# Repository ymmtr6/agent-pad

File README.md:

# AgentPad

RP2040-Zero を使った、8 キー＋ロータリーエンコーダーのマクロパッドです。基板（KiCad）、3D プリント外装・キーキャップ、QMK ファームウェア、VIA 定義をまとめています。

現行版は **Rev2**（単一基板・裏面ホットスワップ）です。

## Rev2 の仕様

- 基板：62 × 80 × 1.6 mm、四隅に M2 用 Ø2.2 mm 穴
- キー：MX 互換スイッチ 8 個（19.05 mm ピッチ、3+3+2 配列）
- ソケット：Kailh CPG151101S11（基板裏面に実装、スイッチは表面から挿す）
- エンコーダー：EC11（右下、押し込み付き）
- MCU：Waveshare RP2040-Zero-M
- USB VID/PID：`0x4150` / `0xA902`

詳しい寸法は [docs/REV2_SINGLE_PCB.md](docs/REV2_SINGLE_PCB.md) と [manifest_rev2.json](manifest_rev2.json) を参照してください。

## デフォルトのキーマップ

| | 左 | 中央 | 右 |
| --- | --- | --- | --- |
| 上段 | F13 | F14 | F15 |
| 中段 | F16 | F17 | F18 |
| 下段 | F19 | F20 | エンコーダー押し込み：Mute |

エンコーダーは反時計回りで音量を下げ、時計回りで上げます。

macOS では F14/F15 が標準で画面の明るさに割り当てられています。システム設定 > キーボード > キーボードショートカット > ディスプレイ で無効にするか、キーを割り当て直してください。

## ファームウェアの書き込み

ビルド済みの UF2 が [firmware/build/](firmware/build/) にあります。

| ファイル | 内容 |
| --- | --- |
| `agent_pad_rev2_via.uf2` | VIA 対応版（キーマップを VIA で変更できる） |
| `agent_pad_rev2_default.uf2` | 固定キーマップ版 |

1. データ通信対応の USB-C ケーブルで PC につなぐ。
2. BOOT と RESET を同時に押し、RESET を離してから BOOT を離す。
3. `RPI-RP2` ドライブが現れたら、UF2 ファイルをコピーする。
4. ドライブが消え、`AgentPad Rev2` として再起動する。

RESET を素早く 2 回押してもブートローダーに入れます。

## VIA でキーマップを変更する

AgentPad は VIA の公式リストに登録していないため、定義ファイルを手動で読み込みます。先に VIA 対応版の UF2 を書き込んでおいてください。

1. [firmware/via/agentpad_rev2.json](firmware/via/agentpad_rev2.json) をダウンロードする。
2. Chrome または Edge で https://usevia.app を開く。
3. Settings で「Show Design tab」を有効にする。
4. Design タブの「Load Draft Definition」で、ダウンロードした JSON を選ぶ。
5. Configure タブで「Authorize device」を押し、`AgentPad Rev2` を選ぶ。

8 キーとエンコーダーの押し込み・左右回転を変更できます。

## ファームウェアのビルド

QMK Firmware の公式リポジトリにキーボード定義をコピーしてビルドします。

```sh
rsync -a firmware/qmk/keyboards/agent_pad/rev2/ \
  /path/to/qmk_firmware/keyboards/agent_pad/rev2/
cd /path/to/qmk_firmware
make agent_pad/rev2:via
```

詳しい手順と検証結果は [firmware/readme.md](firmware/readme.md) にあります。

## 基板の製造

JLCPCB に発注する Gerber は [manufacturing/agentpad_rev2_single_gerber.zip](manufacturing/agentpad_rev2_single_gerber.zip) です。発注設定は [docs/JLCPCB_ORDER_REV2.md](docs/JLCPCB_ORDER_REV2.md)、検証結果は [docs/VALIDATION_REV2.md](docs/VALIDATION_REV2.md) を参照してください。

基板データは生成スクリプトから作り直せます。

```sh
python3 -m venv .venv
.venv/bin/pip install -r requirements.txt
AGENTPAD_OUT=/tmp/agentpad_rev2_single_build .venv/bin/python scripts/generate_agentpad_rev2.py
scripts/run_kicad_drc.sh rev2
```

DRC の実行には KiCad 9 の `kicad-cli` が必要です。

## 外装とキーキャップ

- [cad/rev2_case/](cad/rev2_case/)：3D プリント外装（底トレイ、プレート）の OpenSCAD ソース、STL、G-code
- [cad/keycap_cherry_mx/](cad/keycap_cherry_mx/)：Cherry MX 互換キーキャップ

G-code は Creality Ender-3 V3 SE と PLA 用です。USB 接続での印刷手順は [docs/ENDER3_V3_SE_USB_PRINTING.md](docs/ENDER3_V3_SE_USB_PRINTING.md) を参照してください。

## ディレクトリ構成

| パス | 内容 |
| --- | --- |
| `kicad/` | KiCad 基板データとフットプリント |
| `scripts/` | 基板データの生成スクリプト、DRC 実行スクリプト |
| `gerber/`, `manufacturing/` | 生成済みの Gerber と発注用 ZIP |
| `firmware/` | QMK キーボード定義、ビルド済み UF2、VIA 定義 |
| `cad/` | 外装・キーキャップの 3D データ |
| `docs/` | 設計メモ、発注手順、検証結果、画像 |

Rev1（2 枚構成の旧版）のデータも含まれています。

## ライセンス

[MIT License](LICENSE) です。

ただし `firmware/` 以下は QMK Firmware 向けのコードと、QMK を含めてビルドした UF2 なので、QMK に合わせて GPL-2.0-or-later とします。

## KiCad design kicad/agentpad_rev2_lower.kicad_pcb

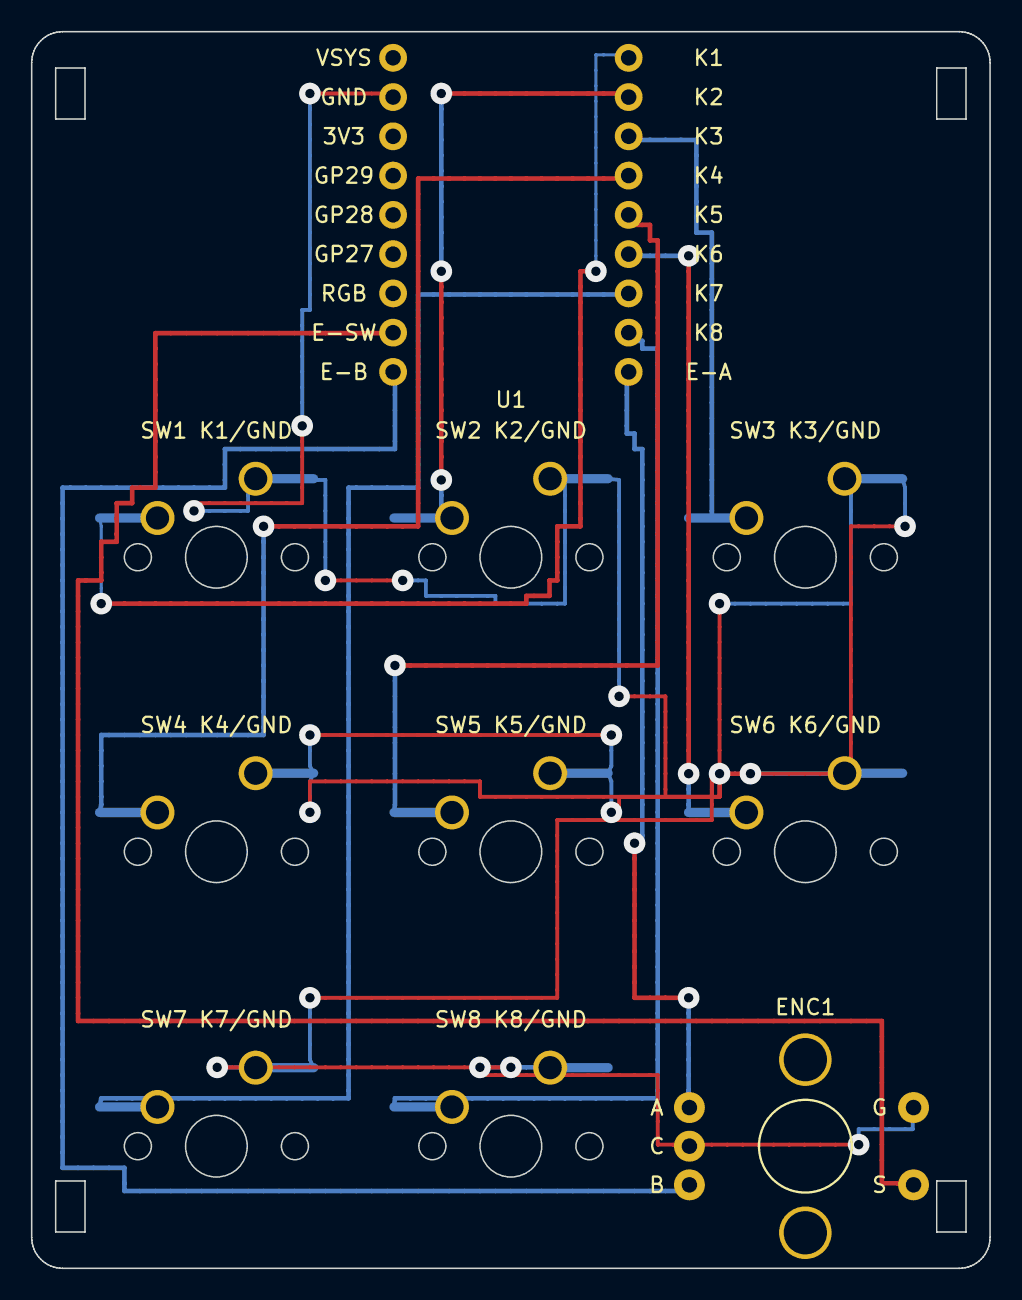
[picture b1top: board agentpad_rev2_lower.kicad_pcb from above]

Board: 2 copper layers, 62.0 x 80.0 mm, 10 parts (0 on the bottom side), 12 nets.

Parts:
ENC1: EC11E push encoder; RotaryEncoder_Alps_EC11E-Switch_Vertical_H20mm
SW1, SW2, SW3, SW4, SW5, SW6, SW7, SW8: Kailh MX Hotswap; Kailh_MX_Hotswap_1U
U1: RP2040-Zero-M (visible top); RP2040-Zero-M_Header_Top

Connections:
ENC_A: ENC1.A, U1.9
ENC_B: ENC1.B, U1.15
ENC_SW: ENC1.S1, U1.16
GND: ENC1.C, ENC1.S2, SW1.2, SW2.2, SW3.2, SW4.2, SW5.2, SW6.2, SW7.2, SW8.2, U1.22
K1: SW1.1, U1.1
K2: SW2.1, U1.2
K3: SW3.1, U1.3
K4: SW4.1, U1.4
K5: SW5.1, U1.5
K6: SW6.1, U1.6
K7: SW7.1, U1.7
K8: SW8.1, U1.8

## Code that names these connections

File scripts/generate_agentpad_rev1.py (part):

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# pin mapping from Waveshare schematic used in previous locked package
pin_signal={
1:'K1',2:'K2',3:'K3',4:'K4',5:'K5',6:'K6',7:'K7',8:'K8',9:'ENC_A',
15:'ENC_B',16:'ENC_SW',17:'RGB',18:'GPIO27',19:'GPIO28',20:'GPIO29',21:'3V3',22:'GND',23:'VSYS'}

# Kailh MX hotswap plated anti-shear-like geometry; switch local coords
# Based on established Kailh MX socket footprints: switch pin holes (-3.81,-2.54),(2.54,-5.08), center 3.9878.
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routes=[]      # (layer, net, width, [points])

signal_ep={**{f'K{i}':(MCU_PINS[i],sw[i]['p1']) for i in range(1,NUM_KEYS+1)},
           'ENC_A':(MCU_PINS[9],enc_pads['A']),
           'ENC_B':(MCU_PINS[15],enc_pads['B']),
           'ENC_SW':(MCU_PINS[16],enc_pads['S1'])}
# Route difficult / distant nets first.
signal_order=[net for net in
              ['K7','K4','K1','K8','K5','K2','ENC_SW','ENC_B','ENC_A','K6','K3']
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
